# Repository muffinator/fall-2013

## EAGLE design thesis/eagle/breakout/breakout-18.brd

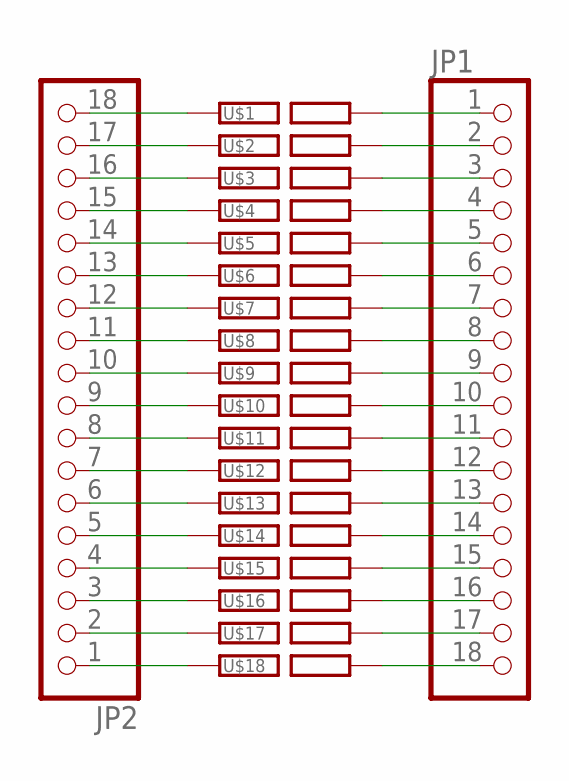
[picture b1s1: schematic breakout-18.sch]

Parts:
JP1, JP2: PINHD-1X18; 1X18
U$1, U$2, U$3, U$4, U$5, U$6, U$7, U$8, U$9, U$10, U$11, U$12, U$13, U$14, U$15, U$16, U$17, U$18: RAILSEP; RAIL

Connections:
unnamed: JP2.18, U$1.P$L (L)
unnamed: JP2.17, U$2.P$L (L)
unnamed: JP2.16, U$3.P$L (L)
unnamed: JP2.15, U$4.P$L (L)
unnamed: JP2.14, U$5.P$L (L)
unnamed: JP2.13, U$6.P$L (L)
unnamed: JP2.12, U$7.P$L (L)
unnamed: JP2.11, U$8.P$L (L)
unnamed: JP2.10, U$9.P$L (L)
unnamed: JP2.9, U$10.P$L (L)
unnamed: JP2.8, U$11.P$L (L)
unnamed: JP2.7, U$12.P$L (L)
unnamed: JP2.6, U$13.P$L (L)
unnamed: JP2.5, U$14.P$L (L)
unnamed: JP2.4, U$15.P$L (L)
unnamed: JP2.3, U$16.P$L (L)
unnamed: JP2.2, U$17.P$L (L)
unnamed: JP2.1, U$18.P$L (L)
unnamed: JP1.1, U$1.P$R (R)
unnamed: JP1.2, U$2.P$R (R)
unnamed: JP1.3, U$3.P$R (R)
unnamed: JP1.4, U$4.P$R (R)
unnamed: JP1.5, U$5.P$R (R)
unnamed: JP1.6, U$6.P$R (R)
unnamed: JP1.7, U$7.P$R (R)
unnamed: JP1.8, U$8.P$R (R)
unnamed: JP1.9, U$9.P$R (R)
unnamed: JP1.10, U$10.P$R (R)
unnamed: JP1.11, U$11.P$R (R)
unnamed: JP1.12, U$12.P$R (R)
unnamed: JP1.13, U$13.P$R (R)
unnamed: JP1.14, U$14.P$R (R)
unnamed: JP1.15, U$15.P$R (R)
unnamed: JP1.16, U$16.P$R (R)
unnamed: JP1.17, U$17.P$R (R)
unnamed: JP1.18, U$18.P$R (R)

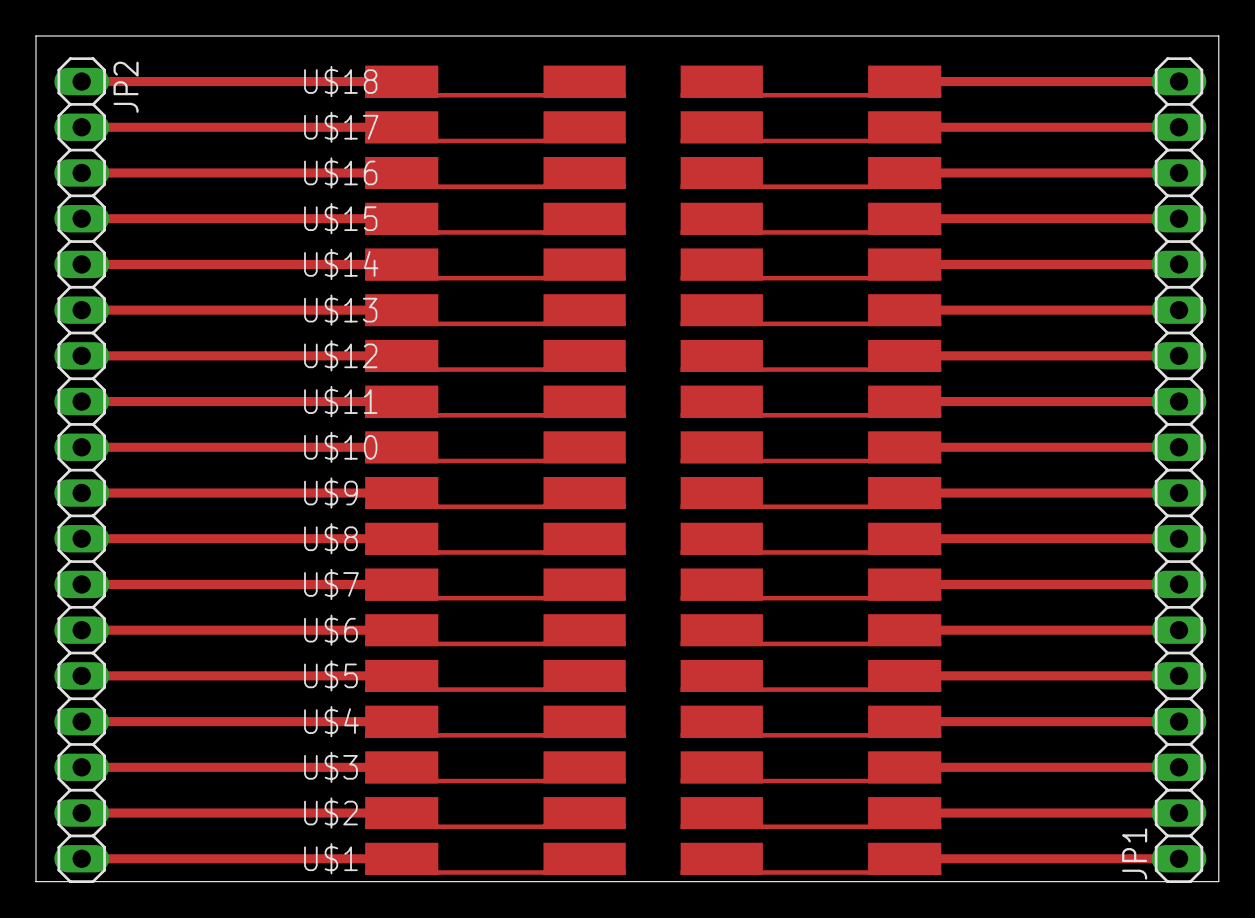
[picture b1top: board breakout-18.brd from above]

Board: 2 copper layers, 65.7 x 47.0 mm, 20 parts (0 on the bottom side), 36 nets.

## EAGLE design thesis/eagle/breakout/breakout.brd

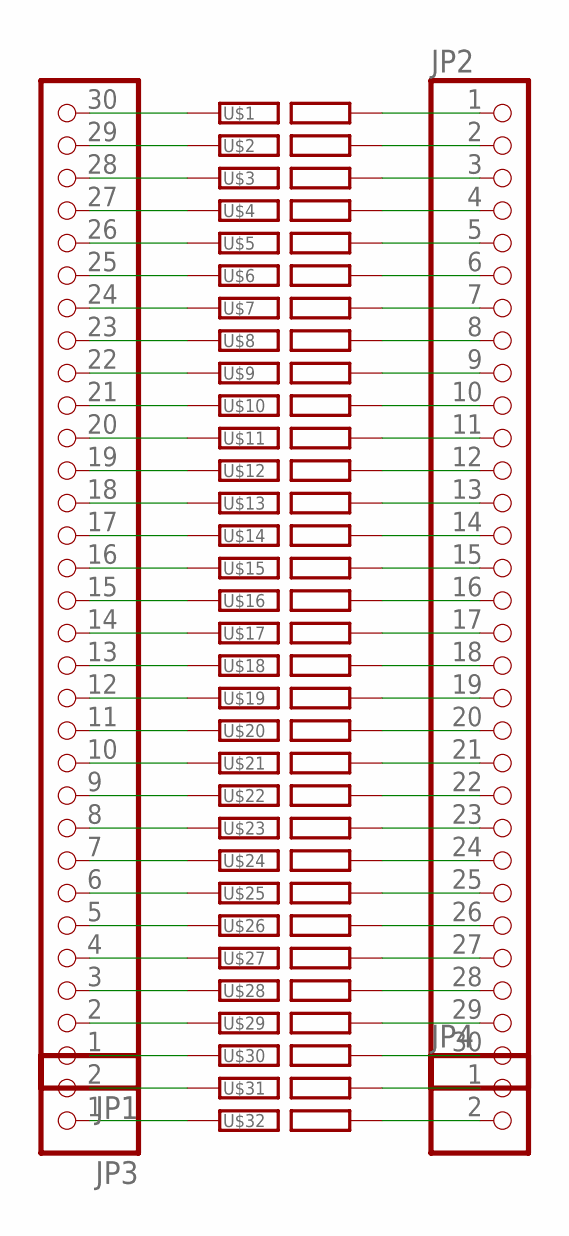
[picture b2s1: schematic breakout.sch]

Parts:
JP1, JP2: PINHD-1X30; 1X30
JP3, JP4: PINHD-1X2; 1X02
U$1, U$2, U$3, U$4, U$5, U$6, U$7, U$8, U$9, U$10, U$11, U$12, U$13, U$14, U$15, U$16, U$17, U$18, U$19, U$20, U$21, U$22, U$23, U$24, U$25, U$26, U$27, U$28, U$29, U$30, U$31, U$32: RAILSEP; RAIL

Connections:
unnamed: JP1.30, U$1.P$L (L)
unnamed: JP1.29, U$2.P$L (L)
unnamed: JP1.28, U$3.P$L (L)
unnamed: JP1.27, U$4.P$L (L)
unnamed: JP1.26, U$5.P$L (L)
unnamed: JP1.25, U$6.P$L (L)
unnamed: JP1.24, U$7.P$L (L)
unnamed: JP1.23, U$8.P$L (L)
unnamed: JP1.22, U$9.P$L (L)
unnamed: JP1.21, U$10.P$L (L)
unnamed: JP1.1, U$30.P$L (L)
unnamed: JP1.20, U$11.P$L (L)
unnamed: JP1.19, U$12.P$L (L)
unnamed: JP1.18, U$13.P$L (L)
unnamed: JP1.17, U$14.P$L (L)
unnamed: JP1.16, U$15.P$L (L)
unnamed: JP1.15, U$16.P$L (L)
unnamed: JP1.14, U$17.P$L (L)
unnamed: JP1.13, U$18.P$L (L)
unnamed: JP1.12, U$19.P$L (L)
unnamed: JP1.11, U$20.P$L (L)
unnamed: JP1.10, U$21.P$L (L)
unnamed: JP1.9, U$22.P$L (L)
unnamed: JP1.8, U$23.P$L (L)
unnamed: JP1.7, U$24.P$L (L)
unnamed: JP1.6, U$25.P$L (L)
unnamed: JP1.5, U$26.P$L (L)
unnamed: JP1.4, U$27.P$L (L)
unnamed: JP1.3, U$28.P$L (L)
unnamed: JP1.2, U$29.P$L (L)
unnamed: JP2.1, U$1.P$R (R)
unnamed: JP2.2, U$2.P$R (R)
unnamed: JP2.3, U$3.P$R (R)
unnamed: JP2.4, U$4.P$R (R)
unnamed: JP2.5, U$5.P$R (R)
unnamed: JP2.6, U$6.P$R (R)
unnamed: JP2.7, U$7.P$R (R)
unnamed: JP2.8, U$8.P$R (R)
unnamed: JP2.9, U$9.P$R (R)
unnamed: JP2.10, U$10.P$R (R)
unnamed: JP2.11, U$11.P$R (R)
unnamed: JP2.12, U$12.P$R (R)
unnamed: JP2.13, U$13.P$R (R)
unnamed: JP2.14, U$14.P$R (R)
unnamed: JP2.15, U$15.P$R (R)
unnamed: JP2.16, U$16.P$R (R)
unnamed: JP2.17, U$17.P$R (R)
unnamed: JP2.18, U$18.P$R (R)
unnamed: JP2.19, U$19.P$R (R)
unnamed: JP2.20, U$20.P$R (R)
unnamed: JP2.21, U$21.P$R (R)
unnamed: JP2.22, U$22.P$R (R)
unnamed: JP2.23, U$23.P$R (R)
unnamed: JP2.24, U$24.P$R (R)
unnamed: JP2.25, U$25.P$R (R)
unnamed: JP2.26, U$26.P$R (R)
unnamed: JP2.27, U$27.P$R (R)
unnamed: JP2.28, U$28.P$R (R)
unnamed: JP2.29, U$29.P$R (R)
unnamed: JP2.30, U$30.P$R (R)
unnamed: JP3.2, U$31.P$L (L)
unnamed: JP3.1, U$32.P$L (L)
unnamed: JP4.1, U$31.P$R (R)
unnamed: JP4.2, U$32.P$R (R)

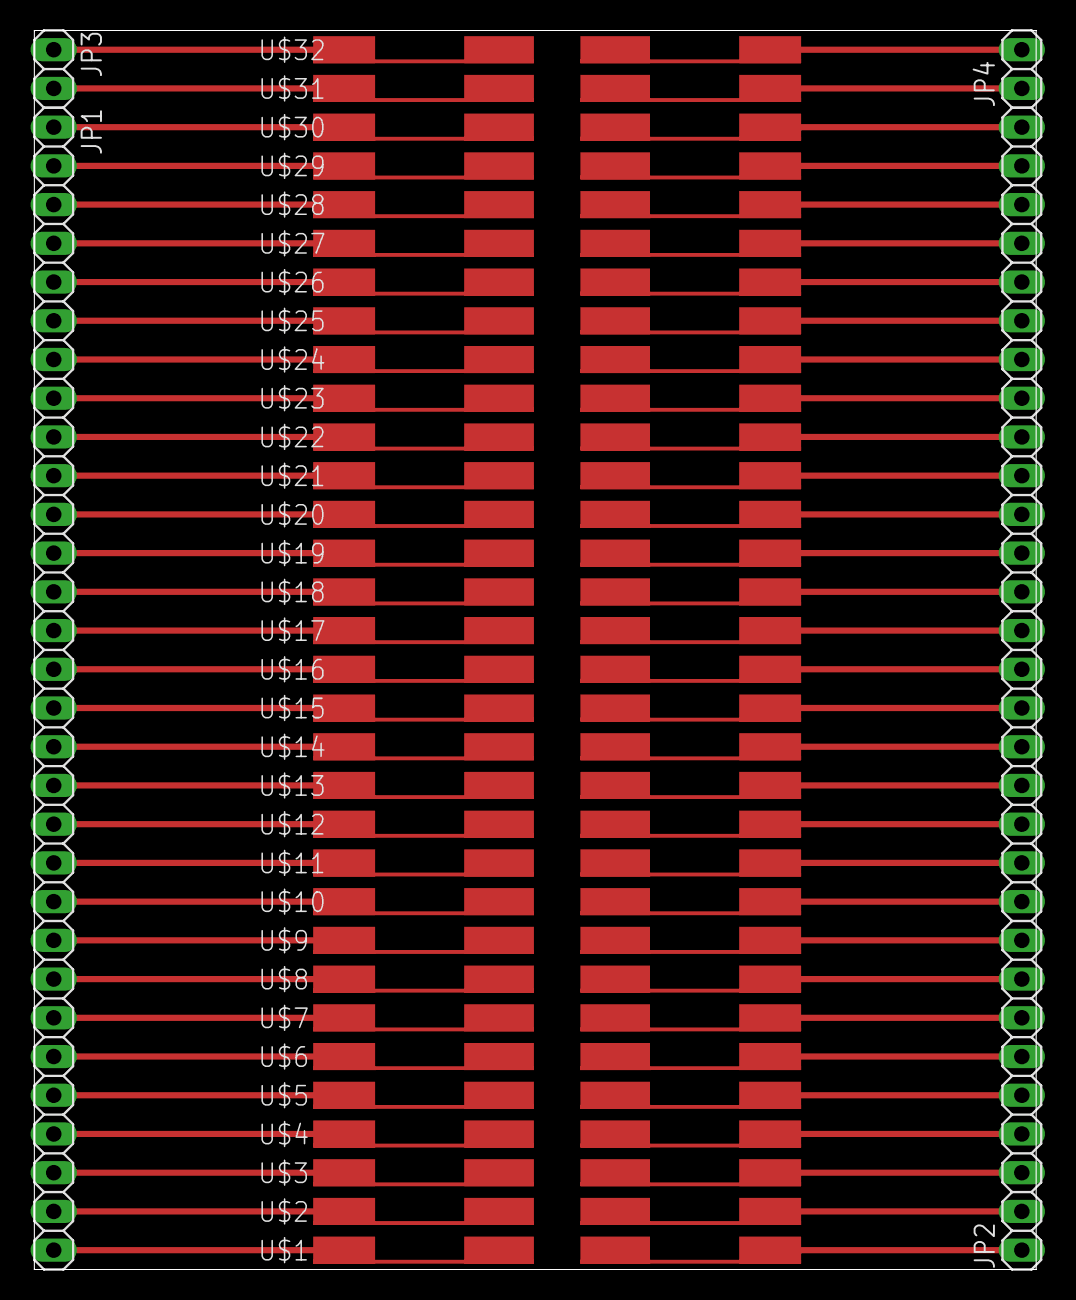
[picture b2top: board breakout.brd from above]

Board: 2 copper layers, 65.7 x 81.3 mm, 36 parts (0 on the bottom side), 64 nets.

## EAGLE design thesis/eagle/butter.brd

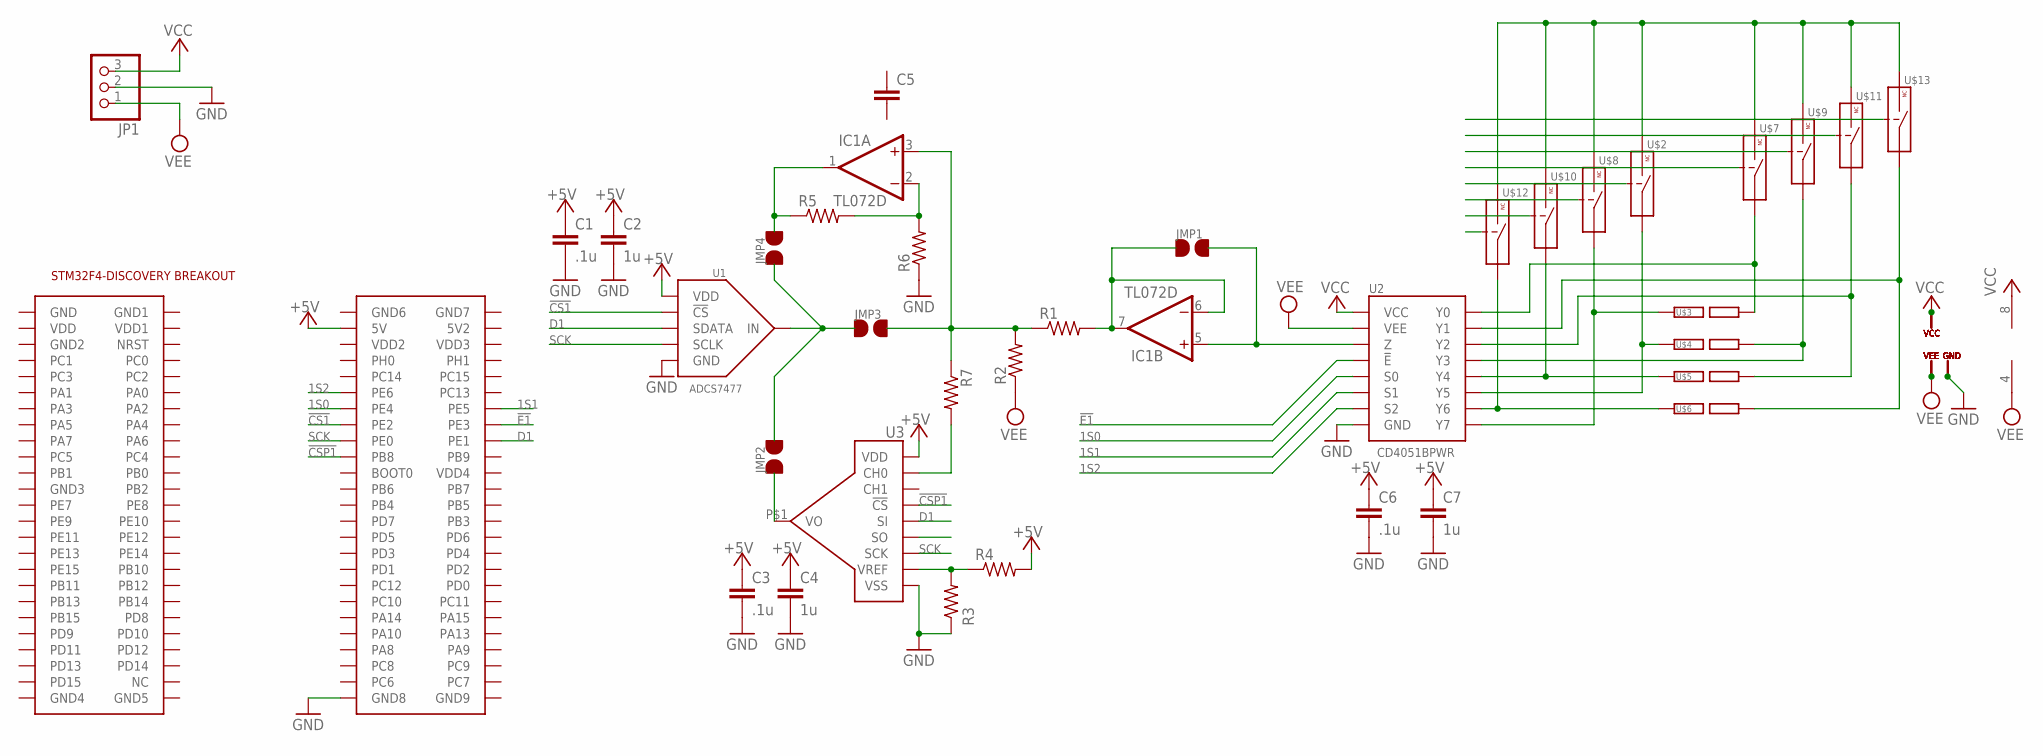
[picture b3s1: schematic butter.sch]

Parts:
C1, C3, C6: .1u; C0805
C2, C4, C7: 1u; C0805
C5: C-EUC0805; C0805
IC1: TL072D; SO08
JMP1, JMP2, JMP3, JMP4: JMP
JP1: PINHD-1X3; 1X03
R1, R2, R3, R4, R5, R6, R7: R-US_R0603; R0603
U1: ADCS7477; SOT-23-6
U2: CD4051BPWR; TSSOP-16
U3: MCP6S93; MSOP-10
U$1: STM32F4-DISCOVERY
U$2, U$7, U$8, U$9, U$10, U$11, U$12, U$13: DG467; TSSOP-6
U$3, U$4, U$5, U$6: RAILSEP; RAIL

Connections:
1S0: U2.P$11 (S0), U$1.P$63 (PE4)
1S1: U2.P$10 (S1), U$1.P$64 (PE5)
1S2: U2.P$9 (S2), U$1.P$61 (PE6)
!CS1: U1.P$6 (!CS), U$1.P$65 (PE2)
!CSP1: U3.P$6 (!CS), U$1.P$69 (PB8)
!E1: U2.P$6 (!E), U$1.P$66 (PE3)
+5V: C1.1, C2.1, C3.1, C4.1, C5.1, C6.1, C7.1, R4.2, U1.P$1 (VDD), U3.P$10 (VDD), U$1.P$53 (5V)
D1: U1.P$5 (SDATA), U3.P$7 (SI), U$1.P$68 (PE1)
GND: C1.2, C2.2, C3.2, C4.2, C5.2, C6.2, C7.2, JP1.2, R3.1, R6.1, U1.P$2 (GND), U2.P$8 (GND), U3.P$5 (VSS), U$1.P$99 (GND8), U$2.P$4 (GND), U$7.P$4 (GND), U$8.P$4 (GND), U$9.P$4 (GND), U$10.P$4 (GND), U$11.P$4 (GND), U$12.P$4 (GND), U$13.P$4 (GND)
unnamed: IC1.2 (-IN), R5.2, R6.2
unnamed: U2.P$13 (Y0), U$3.P$R (R), U$7.P$6 (COM)
unnamed: U2.P$5 (Y5), U$2.P$6 (COM), U$4.P$L (L)
unnamed: IC1.5 (+IN), JMP1.P$2, U2.P$3 (Z)
unnamed: JMP2.P$1, U3.P$1 (VO)
unnamed: IC1.6 (-IN), IC1.7 (OUT), JMP1.P$1, R1.2
unnamed: U2.P$4 (Y7), U$3.P$L (L), U$8.P$6 (COM)
unnamed: U2.P$12 (Y3), U$4.P$R (R), U$9.P$6 (COM)
unnamed: U2.P$1 (Y4), U$5.P$L (L), U$10.P$6 (COM)
unnamed: U2.P$15 (Y2), U$5.P$R (R), U$11.P$6 (COM)
unnamed: U2.P$2 (Y6), U$6.P$L (L), U$12.P$6 (COM)
unnamed: U2.P$14 (Y1), U$6.P$R (R), U$13.P$6 (COM)
unnamed: U$2.P$1 (IN), U$7.P$1 (IN), U$8.P$1 (IN), U$9.P$1 (IN), U$10.P$1 (IN), U$11.P$1 (IN), U$12.P$1 (IN), U$13.P$1 (IN)
unnamed: IC1.3 (+IN), JMP3.P$2, R1.1, R2.2, R7.1
unnamed: R3.2, R4.1, U3.P$4 (VREF)
unnamed: JMP2.P$2, JMP3.P$1, JMP4.P$1, U1.P$3 (IN)
unnamed: IC1.1 (OUT), JMP4.P$2, R5.1
unnamed: R7.2, U3.P$2 (CH0)
SCK: U1.P$4 (SCLK), U3.P$9 (SCK), U$1.P$67 (PE0)
VCC: IC1.8 (V+), JP1.3, U2.P$16 (VCC), U$2.P$5 (VCC), U$7.P$5 (VCC), U$8.P$5 (VCC), U$9.P$5 (VCC), U$10.P$5 (VCC), U$11.P$5 (VCC), U$12.P$5 (VCC), U$13.P$5 (VCC)
VEE: IC1.4 (V-), JP1.1, R2.1, U2.P$7 (VEE), U$2.P$2 (VEE), U$7.P$2 (VEE), U$8.P$2 (VEE), U$9.P$2 (VEE), U$10.P$2 (VEE), U$11.P$2 (VEE), U$12.P$2 (VEE), U$13.P$2 (VEE)

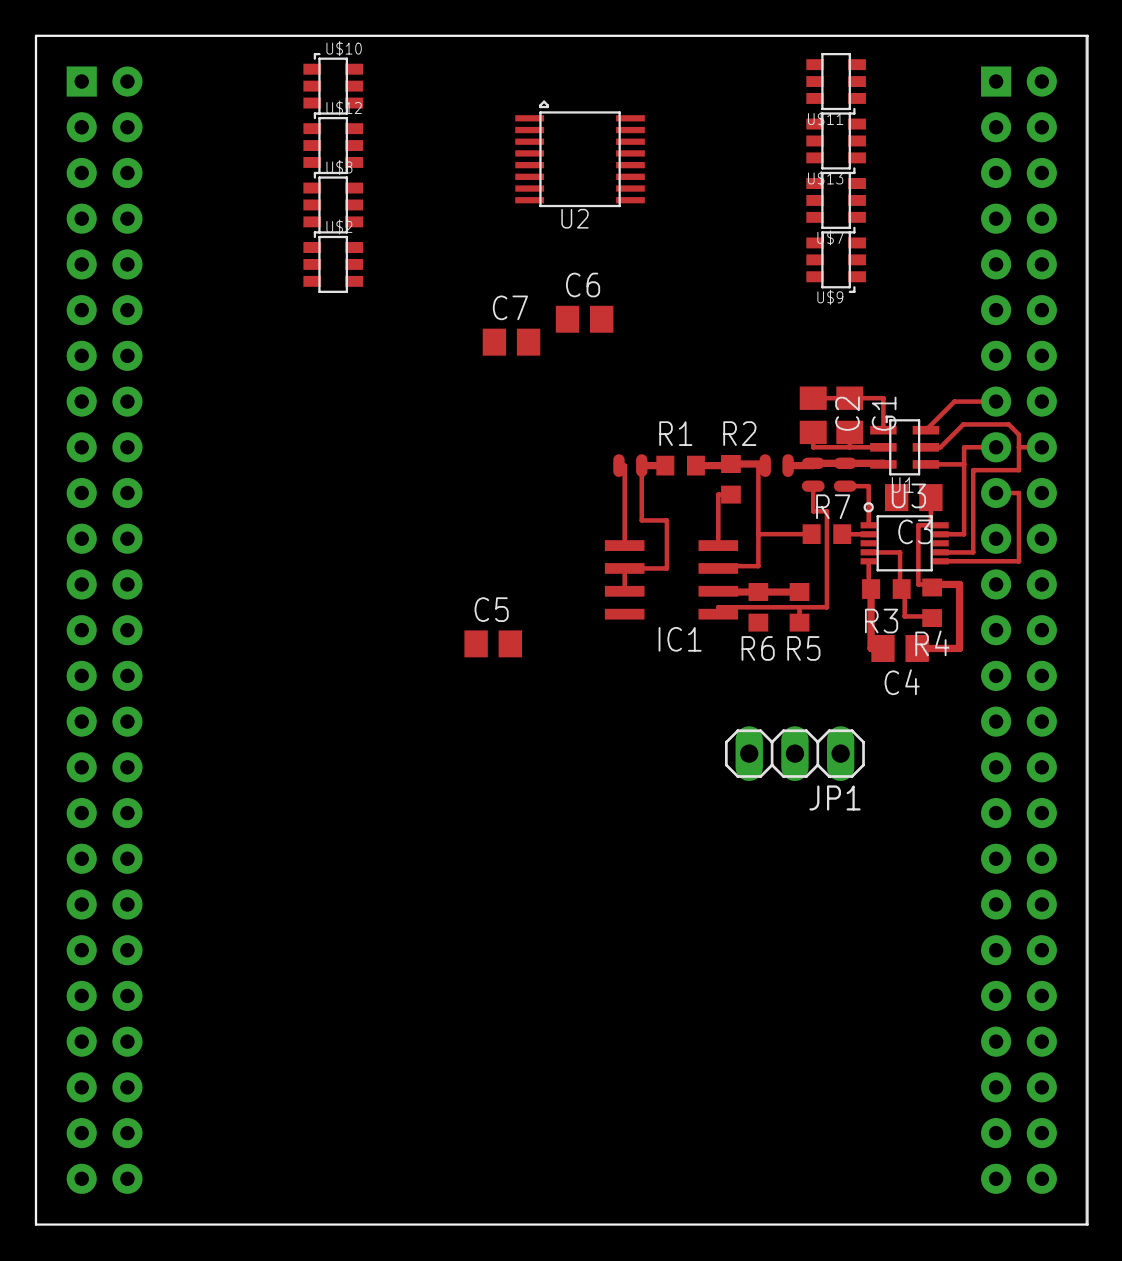
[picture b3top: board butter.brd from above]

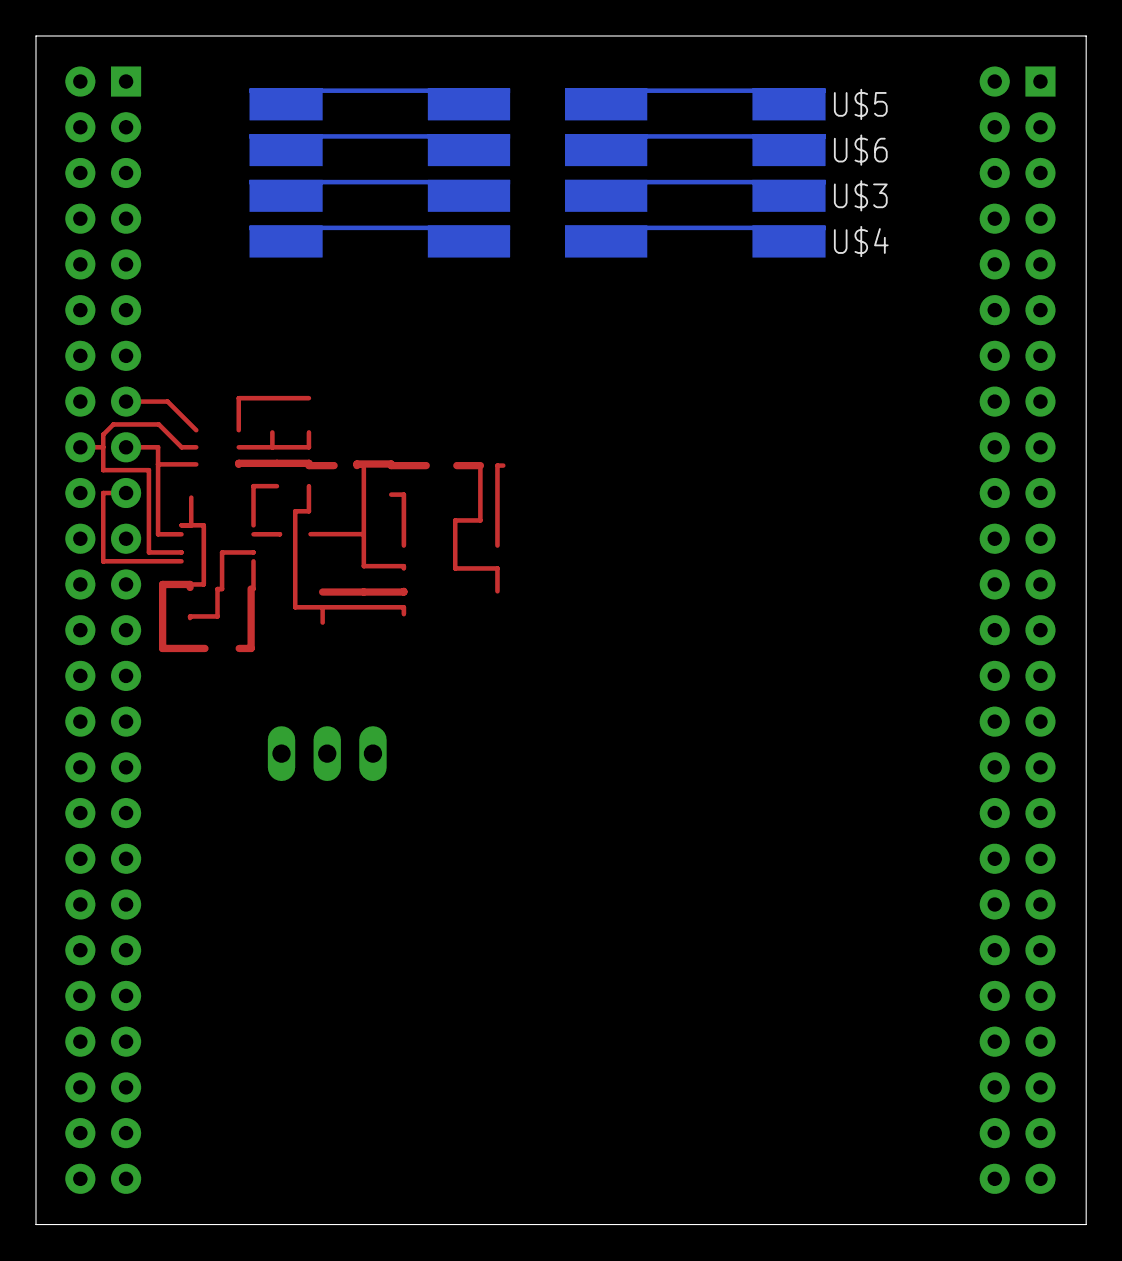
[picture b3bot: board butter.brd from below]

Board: 2 copper layers, 58.3 x 66.0 mm, 36 parts (4 on the bottom side), 30 nets.

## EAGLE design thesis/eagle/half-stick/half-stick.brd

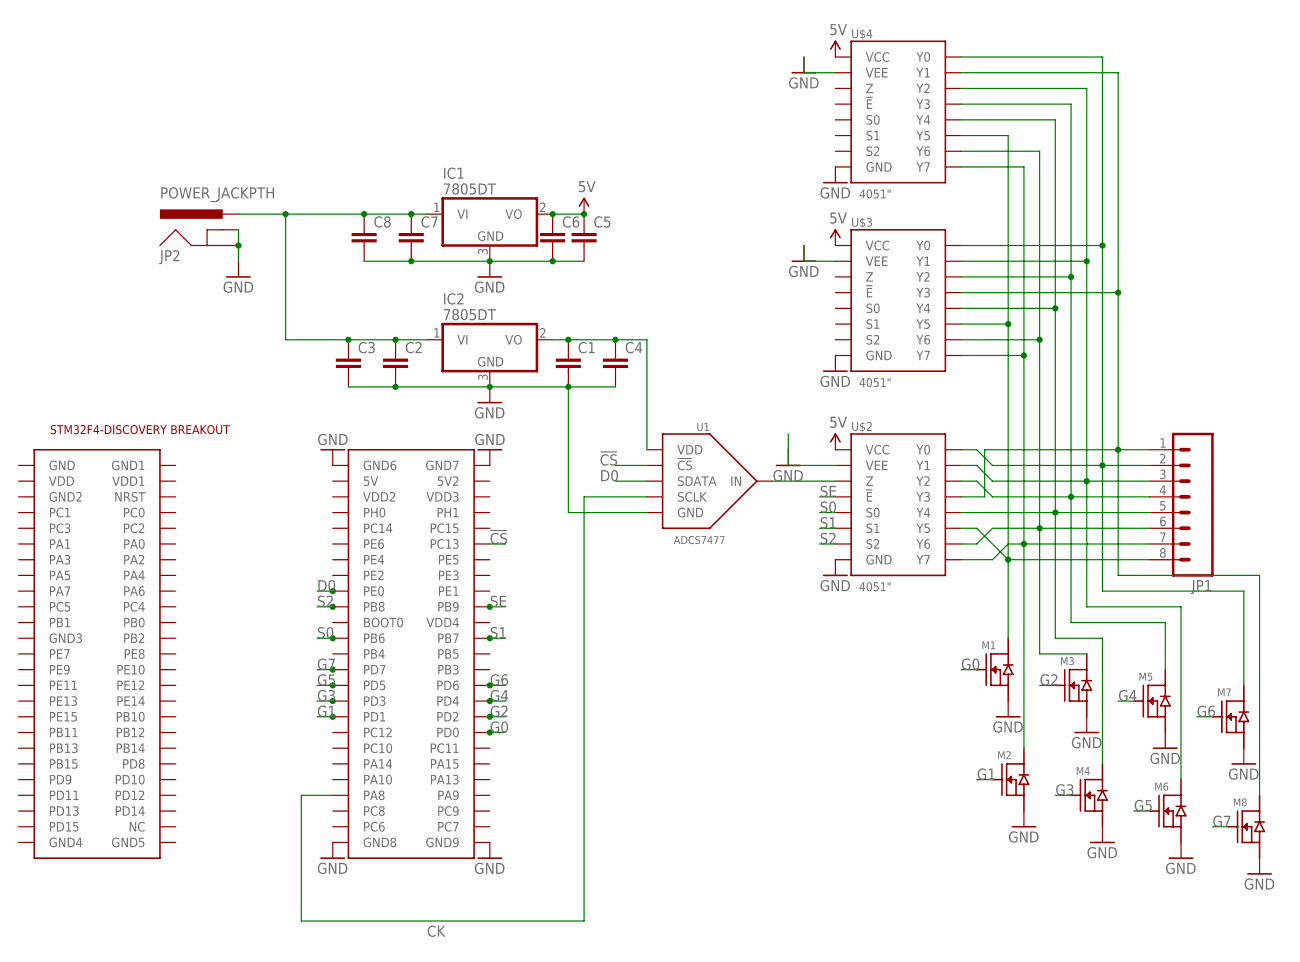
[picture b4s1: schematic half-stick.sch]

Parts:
C1, C2, C3, C4, C5, C6, C7, C8: C-EUC0805; C0805
IC1, IC2: 7805DT; TO252
JP1: M08LONGPADS; 1X08_LONGPADS
JP2: POWER_JACKPTH; POWER_JACK_PTH
M1, M2, M3, M4, M5, M6, M7, M8: N-FET; SOT23-3
U1: ADCS7477; SOT-23-6
U$1: STM32F4-DISCOVERY
U$2, U$3, U$4: 4051"; TSSOP-16

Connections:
5V: C5.1, C6.1, IC1.2 (VO), U$2.P$16 (VCC), U$3.P$16 (VCC), U$4.P$16 (VCC)
!CS: U1.P$6 (!CS), U$1.P$62 (PC13)
CK: U1.P$4 (SCLK), U$1.P$93 (PA8)
D0: U1.P$5 (SDATA), U$1.P$67 (PE0)
G0: M1.1 (G), U$1.P$86 (PD0)
G1: M2.1 (G), U$1.P$83 (PD1)
G2: M3.1 (G), U$1.P$84 (PD2)
G3: M4.1 (G), U$1.P$81 (PD3)
G4: M5.1 (G), U$1.P$82 (PD4)
G5: M6.1 (G), U$1.P$79 (PD5)
G6: M7.1 (G), U$1.P$80 (PD6)
G7: M8.1 (G), U$1.P$77 (PD7)
GND: C1.2, C2.2, C3.2, C4.2, C5.2, C6.2, C7.2, C8.2, IC1.3 (GND), IC2.3 (GND), JP2.GND, JP2.GNDBREAK, M1.2 (S), M2.2 (S), M3.2 (S), M4.2 (S), M5.2 (S), M6.2 (S), M7.2 (S), M8.2 (S), U1.P$2 (GND), U$1.P$51 (GND6), U$1.P$52 (GND7), U$1.P$99 (GND8), U$1.P$100 (GND9), U$2.P$7 (VEE), U$2.P$8 (GND), U$3.P$7 (VEE), U$3.P$8 (GND), U$4.P$7 (VEE), U$4.P$8 (GND)
unnamed: U1.P$3 (IN), U$2.P$3 (Z)
unnamed: C1.1, C4.1, IC2.2 (VO), U1.P$1 (VDD)
unnamed: C2.1, C3.1, C7.1, C8.1, IC1.1 (VI), IC2.1 (VI), JP2.PWR
unnamed: JP1.1, M8.3 (D), U$2.P$12 (Y3), U$3.P$12 (Y3), U$4.P$14 (Y1)
unnamed: JP1.2, M7.3 (D), U$2.P$13 (Y0), U$3.P$13 (Y0), U$4.P$13 (Y0)
unnamed: JP1.3, M6.3 (D), U$2.P$14 (Y1), U$3.P$14 (Y1), U$4.P$15 (Y2)
unnamed: JP1.4, M5.3 (D), U$2.P$15 (Y2), U$3.P$15 (Y2), U$4.P$12 (Y3)
unnamed: JP1.5, M4.3 (D), U$2.P$1 (Y4), U$3.P$1 (Y4), U$4.P$1 (Y4)
unnamed: JP1.6, M3.3 (D), U$2.P$2 (Y6), U$3.P$2 (Y6), U$4.P$2 (Y6)
unnamed: JP1.7, M2.3 (D), U$2.P$4 (Y7), U$3.P$4 (Y7), U$4.P$4 (Y7)
unnamed: JP1.8, M1.3 (D), U$2.P$5 (Y5), U$3.P$5 (Y5), U$4.P$5 (Y5)
S0: U$1.P$73 (PB6), U$2.P$11 (S0)
S1: U$1.P$74 (PB7), U$2.P$10 (S1)
S2: U$1.P$69 (PB8), U$2.P$9 (S2)
SE: U$1.P$70 (PB9), U$2.P$6 (!E)

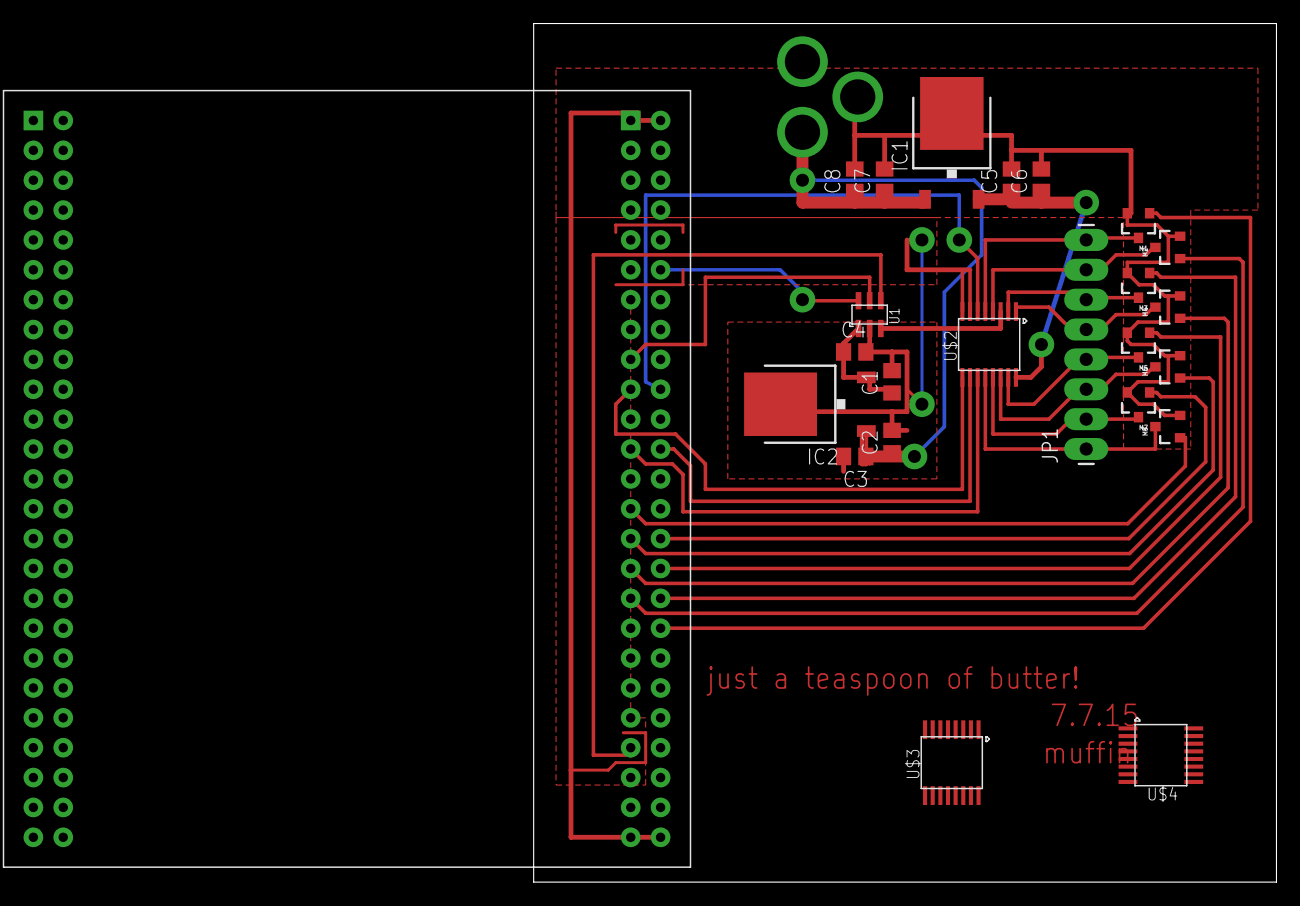
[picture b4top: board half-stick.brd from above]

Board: 2 copper layers, 63.2 x 73.0 mm, 25 parts (1 on the bottom side), 28 nets.

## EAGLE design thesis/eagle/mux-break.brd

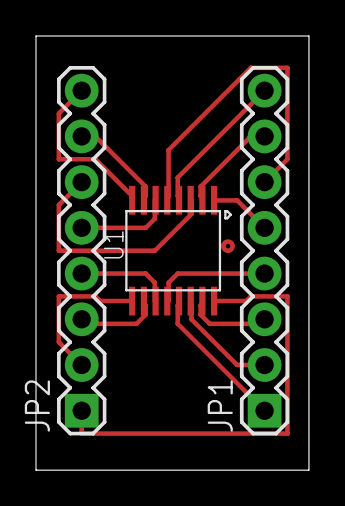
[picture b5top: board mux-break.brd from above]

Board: 2 copper layers, 15.2 x 24.1 mm, 3 parts (0 on the bottom side), 16 nets.

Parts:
JP1, JP2: 1X08
U1: CD4051BPWR; TSSOP-16

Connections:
unnamed: JP1.1, U1.P$13
unnamed: JP1.2, U1.P$14
unnamed: JP1.3, U1.P$15
unnamed: JP1.4, U1.P$12
unnamed: JP1.5, U1.P$1
unnamed: JP1.6, U1.P$5
unnamed: JP1.7, U1.P$2
unnamed: JP1.8, U1.P$4
unnamed: JP2.8, U1.P$8
unnamed: JP2.2, U1.P$9
unnamed: JP2.3, U1.P$10
unnamed: JP2.4, U1.P$11
unnamed: JP2.5, U1.P$6
unnamed: JP2.6, U1.P$3
unnamed: JP2.7, U1.P$7
unnamed: JP2.1, U1.P$16

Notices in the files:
parts and their libraries:
SparkFun-Connectors: Licensing: Creative Commons ShareAlike 4.0 International - https://creativecommons.org/licenses/by-sa/4.0
